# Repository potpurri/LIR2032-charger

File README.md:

# LIR2032 Battery Charging Board

## Overview

Charging board for LIR2032 batteries (or other lithium type button/coin cell batteries with the same diameter and max voltage of 4.2V).

This project features a charging board for LIR2032 batteries. It uses a TP4056 to monitor charging and provides options for safety components. The circuit includes components to manage the charging process efficiently and safely.

Completed PCBs:

## Features

The board includes the following components:

- **TP4056**: For monitoring the charging process.
- **Safety options**: Can use either a DW01A and a FS8205A or a XB7608AJ for safety.
- **P-MOSFETs**: Two P-MOSFETs cut the connection between the battery and the load during charging (if a load is connected to the charging board).
- **Schottky Diode**: Available to forward current from the USB-C charging input to the load during charging.
- **Charging Current Settings (Resistor R9)**: The resistor R9 is used to set the charging current with the following correlations:

| Resistor (Ω) | Charging Current (mA) |
|--------------|------------------------|
| 10k          | 120                    |
| 12k          | 100                    |
| 15k          | 80.0                   |
| 18k          | 66.7                   |
| 22k          | 54.5                   |
| 27k          | 44.4                   |
| 33k          | 36.4                   |
| 39k          | 30.8                   |
| 47k          | 25.5                   |
| 56k          | 21.4                   |
| 68k          | 17.6                   |
| 82k          | 14.6                   |
| 100k         | 12.0                   |

Board being charged with approximately 37mA:

## Images

Below are images of the PCB:

3D render of the front view of the PCB

3D render of the back view of the PCB

Front view of the actual PCB

Back view of the PCB

## Schematics

For detailed schematics, please refer to the [schematic PDF](LIR2032-charger/imgs/schematic.pdf).

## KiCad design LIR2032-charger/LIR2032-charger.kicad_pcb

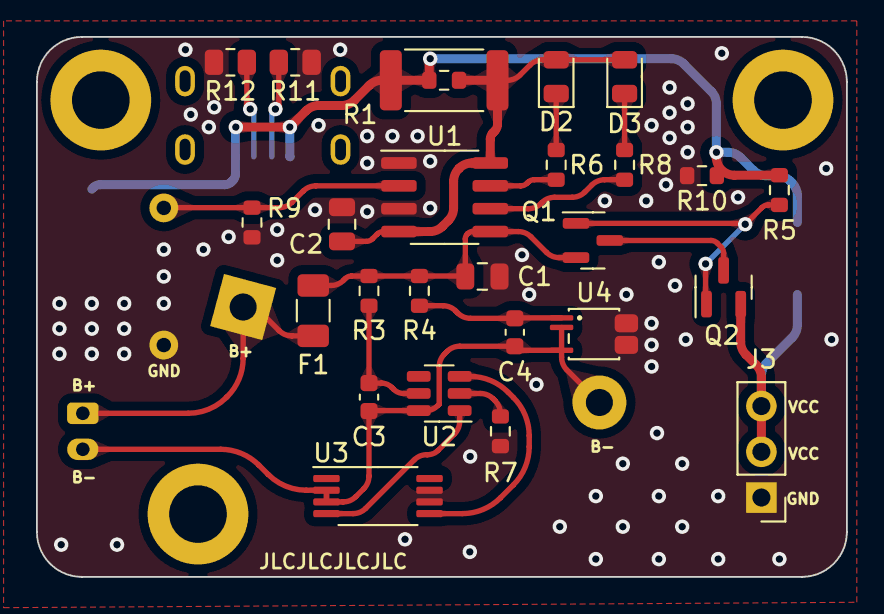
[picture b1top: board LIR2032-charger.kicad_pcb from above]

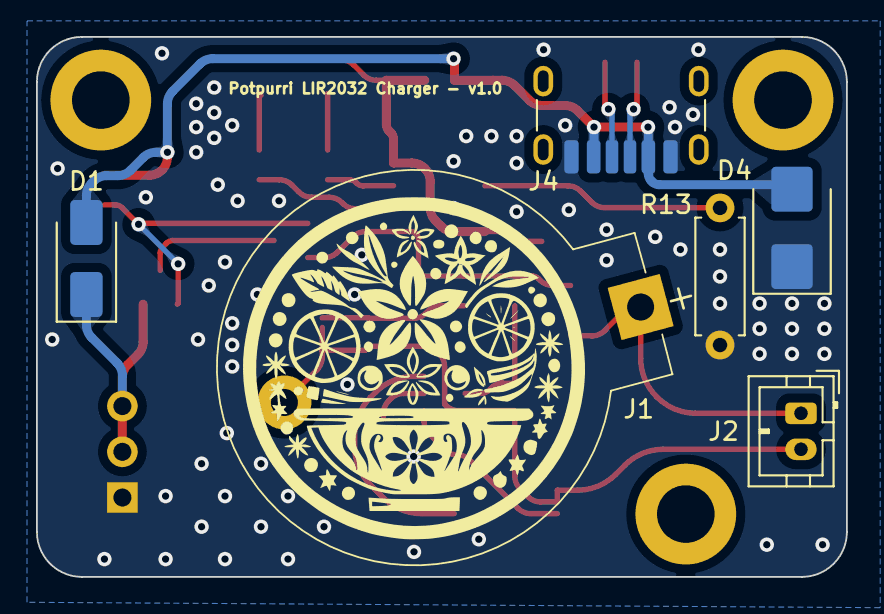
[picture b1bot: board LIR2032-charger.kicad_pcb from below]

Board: 2 copper layers, 45.0 x 30.0 mm, 35 parts (6 on the bottom side), 21 nets.

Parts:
C1, C2: 10u; C_0805_2012Metric
C3, C4: 100n; C_0603_1608Metric
D1: SS34; D_SMA
D2: RED; D_0805_2012Metric
D3: GREEN; D_0805_2012Metric
D4: SMBJ12CA; D_SMB
F1: 1A; Fuse_1206_3216Metric
H1, H2, H3: MountingHole; MountingHole_3.2mm_M3_DIN965_Pad
J1: LIR2032 Connector; CoinCell CR2032
J2: JST PH Connector; JST_PH_B2B-PH-K_1x02_P2.00mm_Vertical
J3: Output; PinHeader_1x03_P2.54mm_Vertical
J4: Type-C_6P; USB-C 6 Pin - Long pads
Q1, Q2: SI2301; SOT-23
R1: 0R4; R_0603_1608Metric
R2: 2512 package; R_2512_6332Metric
R3: 100R; R_0603_1608Metric
R4, R5, R6, R7, R8: 1k; R_0603_1608Metric
R9: 39k; R_0603_1608Metric
R10: 10k; R_0603_1608Metric
R11, R12: 5k1; R_0805_2012Metric
R13: DNF; R_Axial_DIN0207_L6.3mm_D2.5mm_P7.62mm_Horizontal
U1: TP4056; SOP-8_3.76x4.96mm_P1.27mm
U2: DW01A; SOT-23-6
U3: FS8205A; TSSOP-8_4.4x3mm_P0.65mm
U4: XB7608AJ; CPC-5

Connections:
+BATT: F1.1, J1.1, J2.1
-BATT: C3.2, C4.2, J1.2, J2.2, U2.6 (GND), U3.2 (S1), U3.3 (S1), U4.2 (BGND), U4.3 (BGND)
GND: C1.2, C2.2, D4.1 (A1), J3.1, J4.A12 (GND), J4.B12 (GND), R7.2, R9.2, R10.2, R11.2, R12.2, R13.2, U1.1 (TEMP), U1.3 (GND), U3.6 (S2), U3.7 (S2), U4.4 (GND), U4.5 (GND)
unnamed: C2.1, D2.2 (A), D3.2 (A), R1.1, R2.1, U1.4 (VCC), U1.8 (CE)
unnamed: D2.1 (K), R6.1
unnamed: D3.1 (K), R8.1
unnamed: J4.A5 (CC1), R12.1
unnamed: J4.B5 (CC2), R11.1
unnamed: Q1.3 (D), Q2.3 (D)
unnamed: Q1.1 (G), Q2.1 (G), R5.1
unnamed: C1.1, F1.2, Q1.2 (S), R3.2, R4.2, U1.5 (BAT)
unnamed: R6.2, U1.7 (CHRG)
unnamed: R9.1, R13.1, U1.2 (PROG)
unnamed: R8.2, U1.6 (STDBY)
unnamed: U2.3 (OC), U3.5 (G2)
unnamed: U2.1 (OD), U3.4 (G1)
unnamed: C3.1, R3.1, U2.5 (VCC)
unnamed: R7.1, U2.2 (VM)
unnamed: C4.1, R4.1, U4.1 (VCC)
VBUS: D1.2 (A), D4.2 (A2), J4.A9 (VBUS), J4.B9 (VBUS), R1.2, R2.2, R5.2, R10.1
VCC: D1.1 (K), J3.2, J3.3, Q2.2 (S)

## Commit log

2025-01-08 board layout
2025-01-10 Added manufacturing files
2025-02-19 added images and schematic
2025-02-19 added images of pcb
2025-02-19 removed section from readme
